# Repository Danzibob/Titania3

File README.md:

# Titania III
This project is the third iteration of the tiny titania data-logger for model rocketry.

The project goal is to create a datalogger small and light enough for an 18mm A8-3 rocket, but capable enough to use as a backup logger for mid and high power flights.
An additional aim of this project is to run on a rechargable coin cell battery instead of the usual LiPo.
This restriction heavily limits our component choices because of the low current provided by these coin cells (usually <15mA sustained).

## Docs
- [Components List](./hardware/components.md)

## Features
- Logs barometric pressure, temperature, acceleration and rotation data
- Up to 600Hz logging in bursts, 200Hz normal target
- Logs save to flash memory (4MB)
- Buzzer / beeper for basic output & assist in recovery
- PCB-edge USB-A for firmware programming, data offload & charging
- Fits in an 18mm rocket body tube
- Mass of < 10g (including battery)
- LIR1254 rechargable coin cell power source

## Logging format
In order to maximise the logging time available in the flash, we make a trade-off for minimizing storage over precision. This project aims to allow for the following flight timings to fit in the 4MB log flash:

| Flight Phase | Duration (up to) | Storage Priority | Storage Allocation | Max Data Rate |
|---|---|---|---:|---:|
| Pad time | 1 hour | Small constant storage | <1% (~100B) | N/A |
| Ascent | 2 minutes | Most important | ~75% (3 MB) | 25 kB/s |
| Descent | 20 minutes | Less important | ~25% (1 MB) | ~800 B/s |
| Recovery | 2 hours | No storage required | N/A | N/A |

### BMP580
#### Barometric pressure
- Sensor measurement range: 30-125kPa
- Absolute accuracy: +/- 50Pa 
  - Corresponds to ~4m of altitude near sea level
- Relative accuracy: 6Pa per 10kPa
  - ~0.5m / 1km of altitude
  - _Relative accuracy is what's important for determining the altitude of a flight_
- Resolution at oversampling levels (RMS noise @ 100kPa):
  - Low      (1x)   = 0.78Pa @ up to 498Hz
  - Standard (x4)   = 0.41Pa @ up to 255Hz
  - High     (x16)  = 0.21Pa @ up to 87Hz
  - Highest  (x128) = 0.08Pa @ up to 12Hz

On pad, take an f32 Highest resolution sample over a few seconds.
- Massive overkill but nice to have accurate ground pressure

In flight, record u16 pressure with LSB = 2Pa.
- This gives us spatial resolution of ~16cm
- And a range of 0-131kPa, which fully covers the sensor range
- Also easy to convert by bitshifting

#### Temperature
- While ascending, the rocket is moving too fast for the air temperature inside the chassis to equalize
- Therefore, only take temperature readings on the pad and during descent
- Based on the Troposphere lapse rate of ~ 6.5K/km, and the 10km ceiling for this logger, we need to deal with at least a range of 60 degrees
- Combined with a ground temperature range of -10 to 50C this requires a total range of at least 120 degrees
- f16 gives us plenty of resolution within this range

On pad/boot, record a temperature value over several seconds (f16)
- We can combine this with ground pressure for better altitude estimates

Not much point taking temperature readings on ascent
- Could maybe store an i8?

On descent, the barometer will be exposed to the open air at slower speed. 
- Take f16 measurements at regular intervals
- These can be used to accurately profile the air column

#### Sampling & Data Rates
- **Pad** - take a set of samples over a preset startup window (10s?)
  - 6 bytes (f32 pressure and f16 temp)
  - Potentially worth repeating every 30 seconds until launch?
  - Ring buffer to save last N measurements before launch?
- **Ascent** - Log Pressure (and _maybe_ temp) at high frequency
  - 500Hz * u16(+i8) = 1kB/s (1.5kB/s) = 4% (6%) of quota
  - 250Hz * u16(+i8) = 500B/s (750B/s) = 2% (3%) of quota
  - 100Hz * u16(+i8) = 200B/s (300B/s) = <1% (~1%) of quota
- **Descent** - Significantly lower frequency; log pressure & temp at full resolution
  - 10Hz * (u16+f16) = 40B/s = 5% of quota
- **Ground**
  - No logging required

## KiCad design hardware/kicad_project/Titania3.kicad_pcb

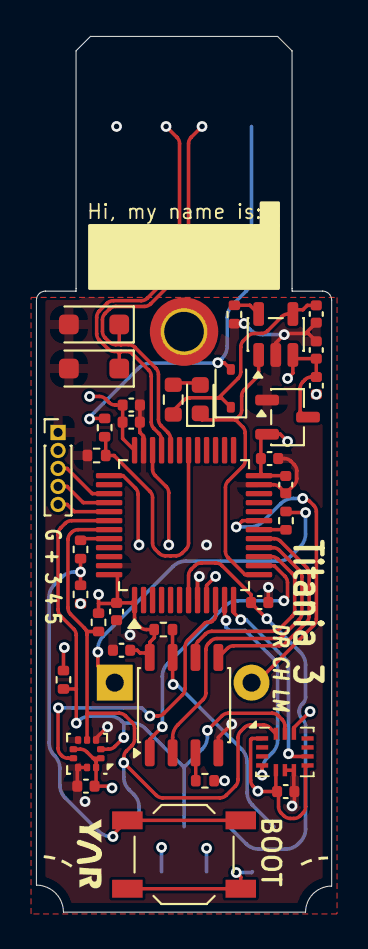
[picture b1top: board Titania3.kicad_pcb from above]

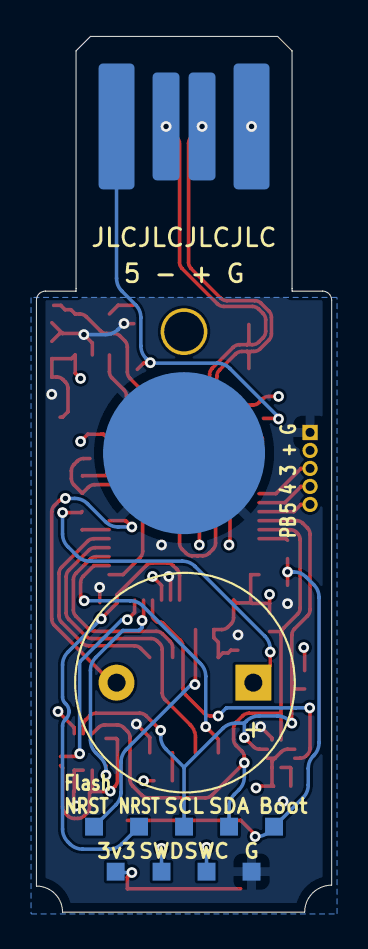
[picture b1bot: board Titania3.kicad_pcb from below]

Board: 4 copper layers, 16.4 x 48.7 mm, 45 parts (11 on the bottom side), 30 nets.

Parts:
3v3: VDD; TestPoint_Pad_1.0x1.0mm
BZ1: Buzzer; Buzzer_12x9.5RM7.6
Boot: BOOT; TestPoint_Pad_1.0x1.0mm
C1, C2, C12: 4.7uF; C_0402_1005Metric
C3, C4: 1.0uF; C_0402_1005Metric
C5, C6, C7, C8, C9, C11, C13: 100nF; C_0402_1005Metric
D1: LED; LED_0603_1608Metric
D2: 1N5819WS; D_SOD-323
D3: BZT52B3V3; D_SOD-123F
D4: BZT52Bxx; D_SOD-123F
FlashNRST: FLASH_NRST; TestPoint_Pad_1.0x1.0mm
G: VSS; TestPoint_Pad_1.0x1.0mm
J1: USB_A; USB_A_PCB_Edge_receptacle
NRST: NRST; TestPoint_Pad_1.0x1.0mm
R1: 470R (>=250mW); R_0603_1608Metric
R2: 68K; R_0402_1005Metric
R3, R4, R5, R6, R8, R9: 10K; R_0402_1005Metric
R7: 470R; R_0402_1005Metric
R10: 33K; R_0402_1005Metric
R11: 82K; R_0402_1005Metric
SCL: SCL; TestPoint_Pad_1.0x1.0mm
SDA: SDA; TestPoint_Pad_1.0x1.0mm
SW1: BOOT; SW_SPST_TL3342
SWC: SWCLK; TestPoint_Pad_1.0x1.0mm
SWD: SWDIO; TestPoint_Pad_1.0x1.0mm
U1: STM32L072CBT6; LQFP-48_7x7mm_P0.5mm
U2: BMI260; Bosch_LGA-14_3x2.5mm_P0.5mm
U3: BMP580; ST_HLGA-10_2x2mm_P0.5mm_LayoutBorder3x2y
U4: MCP73831; SOT-23-5
U5: MX25R3235FM1IL0; JEITA_SOIC-8_3.9x4.9mm_P1.27mm
U6: XC6206P332MR; SOT-23-3

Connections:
+3V3: 3v3.1, C4.1, C5.1, C6.1, C8.2, C9.2, C11.2, C12.1, C13.1, R3.1, R4.1, R8.2, R9.1, SW1.2, U1.1 (VDD), U1.9 (VDDA), U1.24 (VDD), U1.36 (VDD_USB), U1.48 (VDD), U2.1 (SDO), U2.5 (VDDIO), U2.8 (VDD), U2.12 (CSB), U3.1 (VDDIO), U3.6 (CSB), U3.10 (VDD), U5.8 (VCC), U6.2 (VO)
+BATT: C2.1, C3.1, U4.3 (V_{BAT}), U6.3 (VI)
BMI_INT1: U1.11 (PA1), U2.4 (INT1)
BMI_INT2: U1.12 (PA2), U2.9 (INT2)
BMP_INT: U1.10 (PA0), U3.7 (INT)
CHG_STAT: D1.1 (K), U1.13 (PA3), U4.1 (STAT)
FLASH_CS: U1.14 (PA4), U5.1 (~CS)
FLASH_MISO: U1.16 (PA6), U5.2 (SO/SIO1)
FLASH_MOSI: U1.17 (PA7), U5.5 (SI/SIO0)
FLASH_SCK: U1.15 (PA5), U5.6 (SCLK)
GND: C1.2, C2.2, C3.2, C4.2, C5.2, C6.2, C7.1, C8.1, C9.1, C11.1, C12.2, C13.2, D3.2 (A), D4.2 (A), G.1, J1.4 (GND), R2.1, R5.1, R11.2, U1.8 (VSSA), U1.23 (VSS), U1.35 (VSS), U1.47 (VSS), U2.6 (GNDIO), U2.7 (GND), U3.3 (VSS), U3.5 (SDO), U3.8 (VSS), U3.9 (VSS), U4.2 (V_{SS}), U5.4 (GND), U6.1 (GND)
NRST: C7.2, NRST.1, U1.7 (NRST)
unnamed: BZ1.1 (+), R7.1
unnamed: BZ1.2 (-), U1.19 (PB1)
unnamed: D1.2 (A), R1.2
unnamed: C1.1, D2.1 (K), R1.1, U4.4 (V_{DD})
unnamed: Boot.1, R5.2, R6.2, SW1.1
unnamed: R6.1, U1.44 (BOOT0)
unnamed: R10.2, R11.1, U1.30 (PA9)
unnamed: R7.2, U1.18 (PB0)
unnamed: R2.2, U4.5 (PROG)
unnamed: FlashNRST.1, R9.2, U5.7 (~RESET/SIO3)
unnamed: R8.1, U5.3 (~WP/SIO2)
SCL: R3.2, SCL.1, U1.42 (PB6), U2.13 (SCx), U3.2 (SCK)
SDA: R4.2, SDA.1, U1.43 (PB7), U2.14 (SDx), U3.4 (SDI)
SWCLK: SWC.1, U1.37 (PA14)
SWDIO: SWD.1, U1.34 (PA13)
USB_D+: D4.1 (K), J1.3 (D+), U1.33 (PA12)
USB_D-: D3.1 (K), J1.2 (D-), U1.32 (PA11)
USB_VBUS: D2.2 (A), J1.1 (VBUS), R10.1

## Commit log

2026-02-25 Link to components .md
2026-02-25 Add todo note
2026-02-26 More notes on Baro precision and data rates
